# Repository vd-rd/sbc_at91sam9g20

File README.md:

View this project on [CADLAB.io](https://cadlab.io/project/30536). 

# Microchip AT91SAM9G20

## Description
 The follow-up to my previous [SBC based on AT91SAM9260](https://github.com/vd-rd/sbc_at91sam9260), enhancing the board specs in computing power and flexibility. The board is smaller 60x40mm now (SAM9260 was 80x40mm) while keeping the same amount of supported RAM and interfaces. AT91SAM9G20 boosts core speed to 400MHz and bus speed to 133MHz.
 
Board overview (draft):
[TBD]

### Features

| Characteristic | Description |
| --- | --- |
| Dimensions | 60mm x 40mm |
| Processor | AT91SAM9G20 - ARM926EJ @ 400MHz |
| Oscillators |  18.432MHz main clock, 32.768kHz RTC |
| RAM | SDRAM 128MB max (2x512Mbit modules) |
| Storage | microSD |
| USB | 1 microUSB client, 2 USB Host|
| Ethernet | RMII header |
| WiFi/BT | N/A |
| Supply | USB 5V, ACIN 5V |

Common interfaces such as I2C, SPI, UART and GPIO are exposed on the header.

### Building and flashing

Build U-Boot and Linux kernel + rootFS - TBD

Flash to SDCard - TBD

### Resources

You can find all necesary information to build or evaluate the module here:
   - [Fabrication files](https://github.com/vd-rd/sbc_alw_a13/releases)

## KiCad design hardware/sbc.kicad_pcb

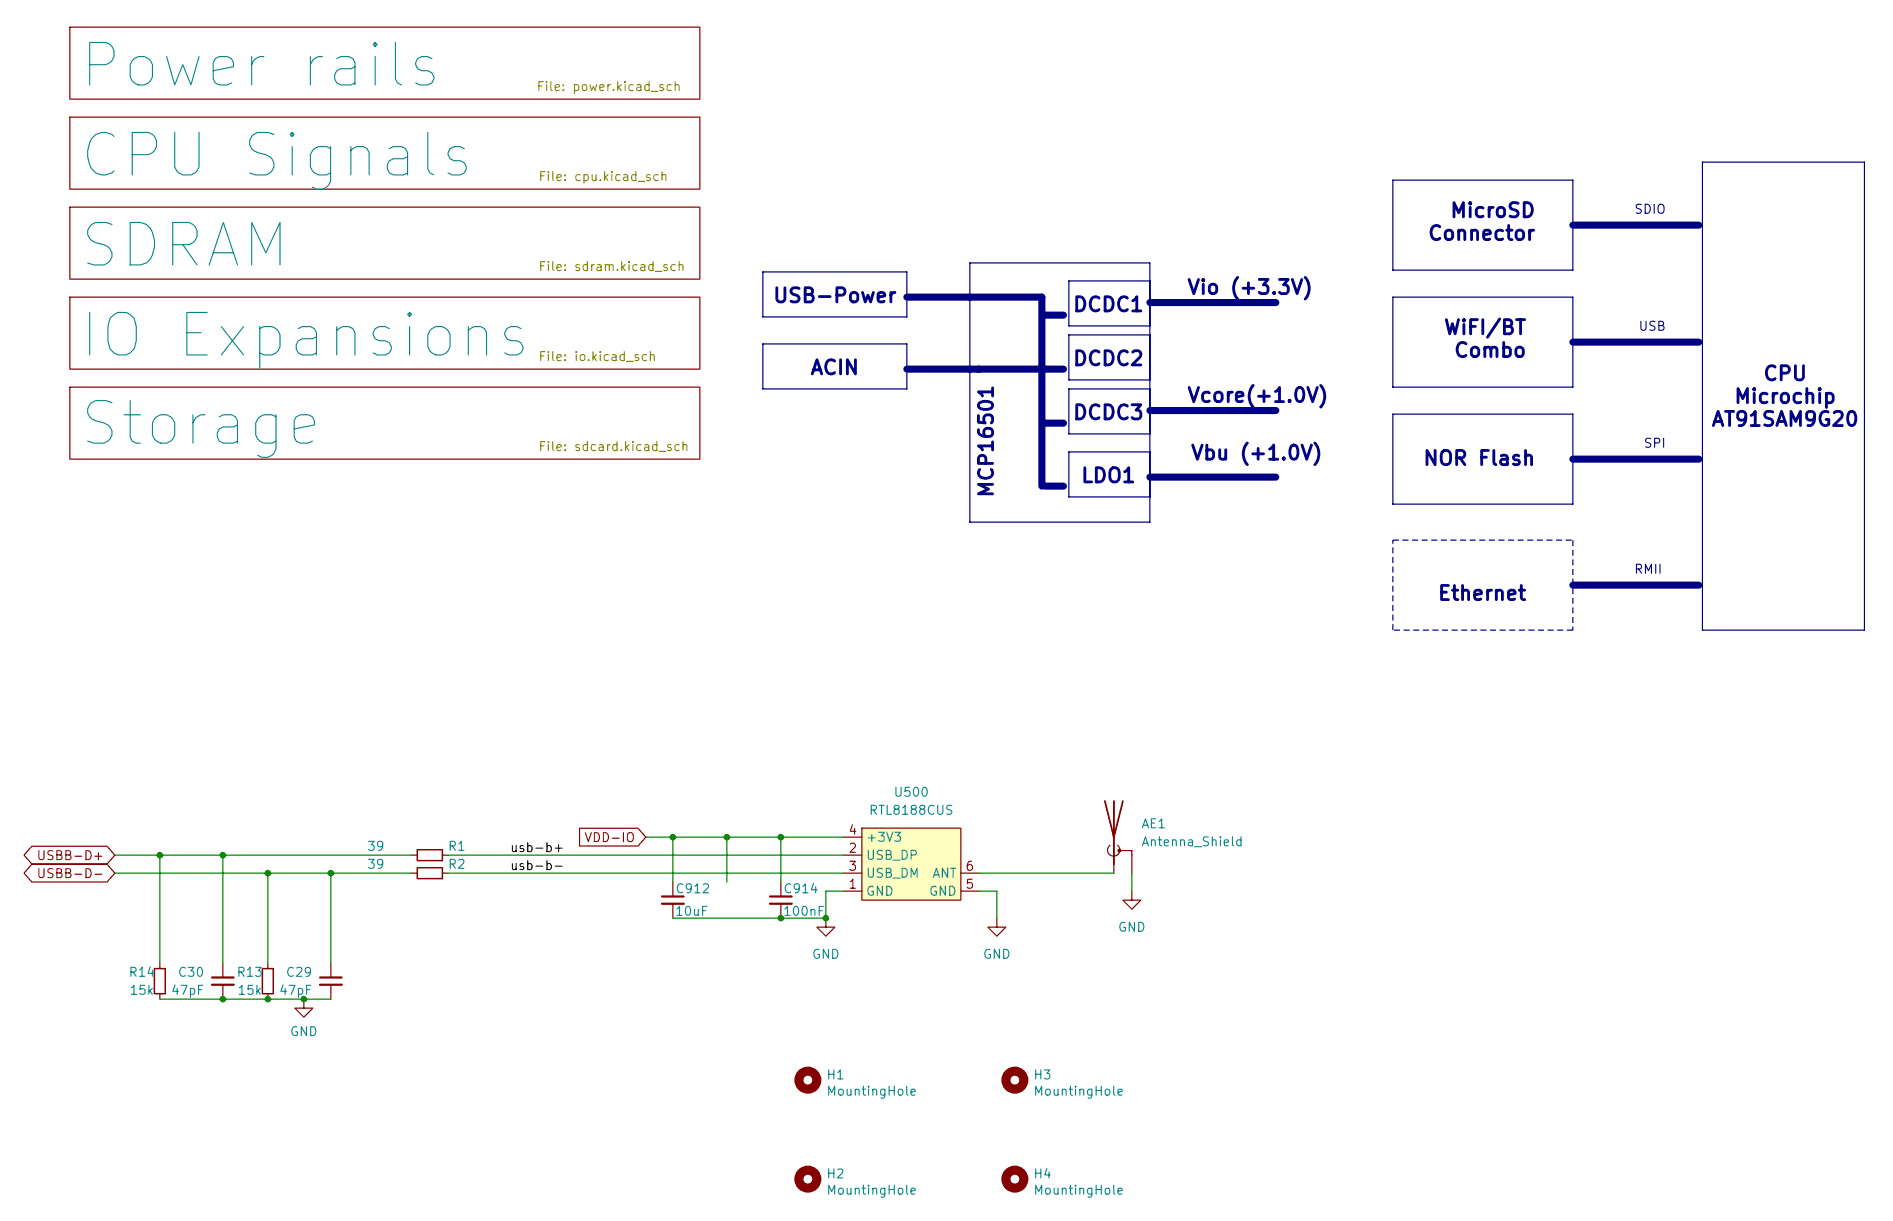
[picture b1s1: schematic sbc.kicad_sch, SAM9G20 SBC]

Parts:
AE1: Antenna_Shield; U.FL_Hirose_U.FL-R-SMT-1_Vertical
C29, C30: 47pF; C_0402_1005Metric
C912: 10uF; C_0603_1608Metric
C914: 100nF; C_0402_1005Metric
H1, H2, H3, H4: MountingHole; MountingHole_2.7mm_M2.5_DIN965
R1, R2: 39; R_0402_1005Metric
R13, R14: 15k; R_0402_1005Metric
U500: RTL8188CUS

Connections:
/usb-b+: R1.1, U500.2 (USB_DP)
/usb-b-: R2.1, U500.3 (USB_DM)
GND: AE1.2 (Shield), C29.2, C30.2, C912.2, C914.2, R13.2, R14.2, U500.1 (GND), U500.5 (GND); also elsewhere on the board
unnamed: AE1.1 (A), U500.6 (ANT)
USBB-D+: C30.1, R1.2, R14.1; also elsewhere on the board
USBB-D-: C29.1, R2.2, R13.1; also elsewhere on the board
VDD-IO: C912.1, C914.1, U500.4 (+3V3); also elsewhere on the board

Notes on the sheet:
Vbu (+1.0V)
DCDC3
USB-Power
NOR Flash
MCP16501
CPU Microchip AT91SAM9G20
Ethernet
ACIN
USB
WiFI/BT Combo
DCDC2
Vcore(+1.0V)
LDO1
DCDC1
MicroSD Connector
SPI
RMII
Vio (+3.3V)
SDIO

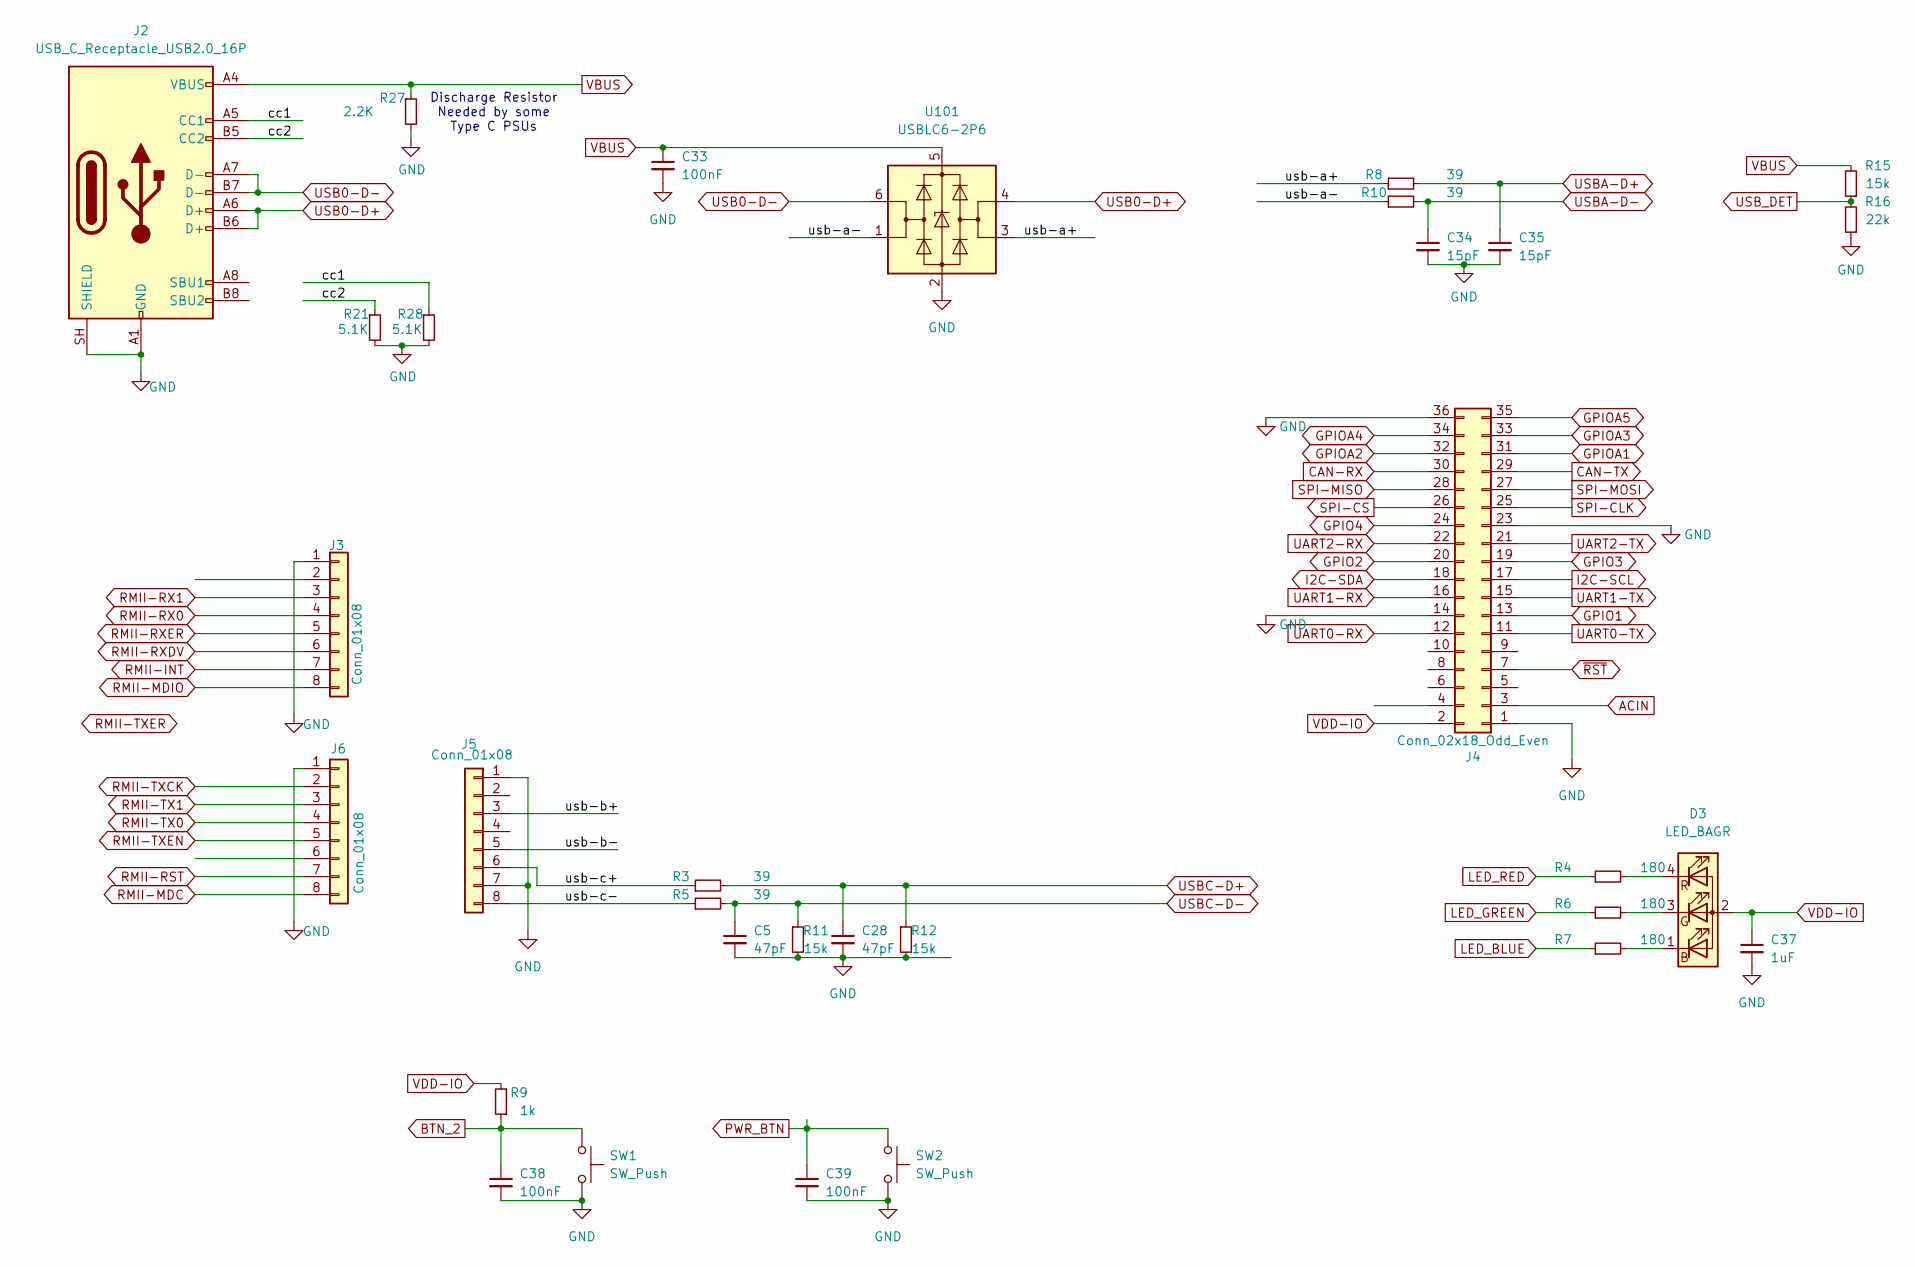
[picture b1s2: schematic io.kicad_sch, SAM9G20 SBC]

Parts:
C5, C28: 47pF; C_0402_1005Metric
C33, C38, C39: 100nF; C_0402_1005Metric
C34, C35: 15pF; C_0402_1005Metric
C37: 1uF; C_0402_1005Metric
D3: LED_BAGR; LED_RGB_Optosupply_OSTB0805C1E-A-0.8T
J2: USB_C_Receptacle_USB2.0_16P; USB_C_Receptacle_GCT_USB4105-xx-A_16P_TopMnt_Horizontal
J3, J5, J6: Conn_01x08; PinHeader_2x04_P1.27mm_Vertical
J4: Conn_02x18_Odd_Even; PinHeader_2x18_P2.54mm_Vertical
R3, R5, R8, R10: 39; R_0402_1005Metric
R4, R6, R7: 180; R_0402_1005Metric
R9: 1k; R_0402_1005Metric
R11, R12, R15: 15k; R_0402_1005Metric
R16: 22k; R_0402_1005Metric
R21, R28: 5.1K; R_0402_1005Metric; Part Description Resistor 2.2K M1005 1% 63mW
R27: 2.2K; R_0402_1005Metric; Part Description Resistor 2.2K M1005 1% 63mW
SW1, SW2: SW_Push; SW_SPST_EVQP7C
U101: USBLC6-2P6; SOT-23-6

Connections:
/IO Expansions/cc1: J2.A5 (CC1), R28.1
/IO Expansions/cc2: J2.B5 (CC2), R21.1
/IO Expansions/usb-a+: R8.1, U101.3 (I/O2)
/IO Expansions/usb-a-: R10.1, U101.1 (I/O1)
/IO Expansions/usb-b+: J5.3
/IO Expansions/usb-b-: J5.5
/IO Expansions/usb-c+: J5.6, R3.1
/IO Expansions/usb-c-: J5.8, R5.1
ACIN: J4.3; also elsewhere on the board
BTN_2: C38.1, R9.1, SW1.1; also elsewhere on the board
CAN-RX: J4.30
CAN-TX: J4.29
GND: C5.2, C28.2, C33.2, C34.2, C35.2, C37.2, C38.2, C39.2, J2.A1 (GND), J2.A12 (GND), J2.B1 (GND), J2.B12 (GND), J2.SH (SHIELD), J3.1, J4.1, J4.14, J4.23, J4.36, J5.1, J5.7, J6.1, R11.2, R12.2, R16.1, R21.2, R27.2, R28.2, SW1.2, SW2.2, U101.2 (GND); also elsewhere on the board
GPIO1: J4.13; also elsewhere on the board
GPIO2: J4.20; also elsewhere on the board
GPIO3: J4.19; also elsewhere on the board
GPIO4: J4.24; also elsewhere on the board
GPIOA1: J4.31; also elsewhere on the board
GPIOA2: J4.32; also elsewhere on the board
GPIOA3: J4.33; also elsewhere on the board
GPIOA4: J4.34; also elsewhere on the board
GPIOA5: J4.35
I2C-SCL: J4.17; also elsewhere on the board
I2C-SDA: J4.18; also elsewhere on the board
LED_BLUE: R7.1; also elsewhere on the board
LED_GREEN: R6.1; also elsewhere on the board
LED_RED: R4.1; also elsewhere on the board
unnamed: D3.1 (BK), R7.2
unnamed: D3.3 (GK), R6.2
unnamed: D3.4 (RK), R4.2
PWR_BTN: C39.1, SW2.1; also elsewhere on the board
RMII-INT: J3.7
RMII-MDC: J6.8; also elsewhere on the board
RMII-MDIO: J3.8; also elsewhere on the board
RMII-RST: J6.7
RMII-RX0: J3.4; also elsewhere on the board
RMII-RX1: J3.3; also elsewhere on the board
RMII-RXDV: J3.6; also elsewhere on the board
RMII-RXER: J3.5; also elsewhere on the board
RMII-TX0: J6.4; also elsewhere on the board
RMII-TX1: J6.3; also elsewhere on the board
RMII-TXCK: J6.2; also elsewhere on the board
RMII-TXEN: J6.5; also elsewhere on the board
SPI-CLK: J4.25; also elsewhere on the board
SPI-CS: J4.26; also elsewhere on the board
SPI-MISO: J4.28; also elsewhere on the board
SPI-MOSI: J4.27; also elsewhere on the board
UART0-RX: J4.12; also elsewhere on the board
UART0-TX: J4.11; also elsewhere on the board
UART1-RX: J4.16; also elsewhere on the board
UART1-TX: J4.15; also elsewhere on the board
UART2-RX: J4.22; also elsewhere on the board
UART2-TX: J4.21; also elsewhere on the board
USB0-D+: J2.A6 (D+), J2.B6 (D+), U101.4 (I/O2)
USB0-D-: J2.A7 (D-), J2.B7 (D-), U101.6 (I/O1)
USBA-D+: C35.1, R8.2; also elsewhere on the board
USBA-D-: C34.1, R10.2; also elsewhere on the board
USBC-D+: C28.1, R3.2, R12.1; also elsewhere on the board
USBC-D-: C5.1, R5.2, R11.1; also elsewhere on the board
USB_DET: R15.1, R16.2; also elsewhere on the board
VBUS: C33.1, J2.A4 (VBUS), J2.A9 (VBUS), J2.B4 (VBUS), J2.B9 (VBUS), R15.2, R27.1, U101.5 (VBUS); also elsewhere on the board
VDD-IO: C37.1, D3.2 (A), J4.2, R9.2; also elsewhere on the board
~RST: J4.7; also elsewhere on the board

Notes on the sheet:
Discharge Resistor Needed by some Type C PSUs

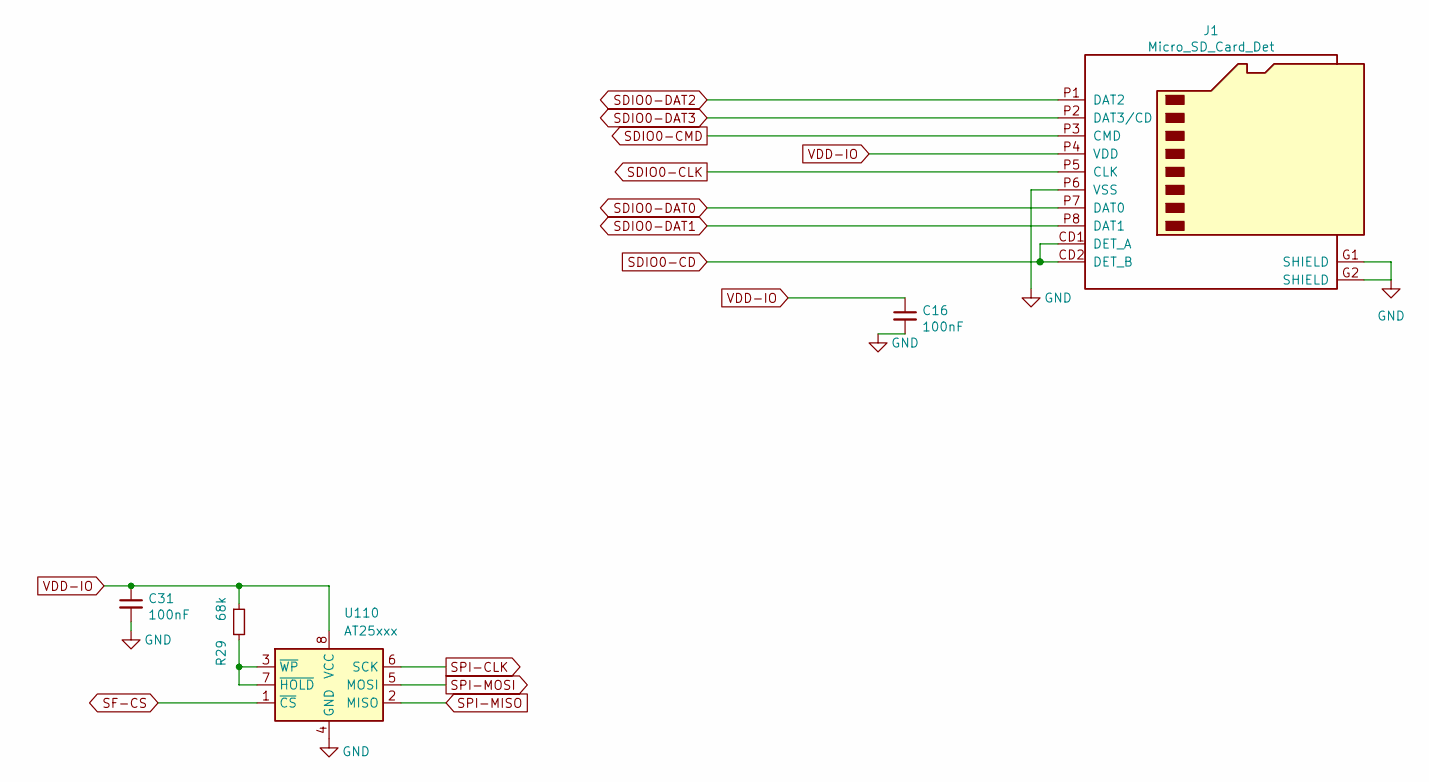
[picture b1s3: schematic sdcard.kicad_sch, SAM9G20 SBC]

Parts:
C16, C31: 100nF; C_0402_1005Metric
J1: Micro_SD_Card_Det; MEM20610118800A
R29: 68k; R_0402_1005Metric
U110: AT25xxx; SOIC-8_5.23x5.23mm_P1.27mm

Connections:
GND: C16.2, C31.2, J1.G1 (SHIELD), J1.G2 (SHIELD), J1.P6 (VSS), U110.4 (GND); also elsewhere on the board
unnamed: R29.2, U110.3 (~WP), U110.7 (~HOLD)
SDIO0-CD: J1.CD1 (DET_A), J1.CD2 (DET_B); also elsewhere on the board
SDIO0-CLK: J1.P5 (CLK); also elsewhere on the board
SDIO0-CMD: J1.P3 (CMD); also elsewhere on the board
SDIO0-DAT0: J1.P7 (DAT0); also elsewhere on the board
SDIO0-DAT1: J1.P8 (DAT1); also elsewhere on the board
SDIO0-DAT2: J1.P1 (DAT2); also elsewhere on the board
SDIO0-DAT3: J1.P2 (DAT3/CD); also elsewhere on the board
SF-CS: U110.1 (~CS); also elsewhere on the board
SPI-CLK: U110.6 (SCK); also elsewhere on the board
SPI-MISO: U110.2 (MISO); also elsewhere on the board
SPI-MOSI: U110.5 (MOSI); also elsewhere on the board
VDD-IO: C16.1, C31.1, J1.P4 (VDD), R29.1, U110.8 (VCC); also elsewhere on the board

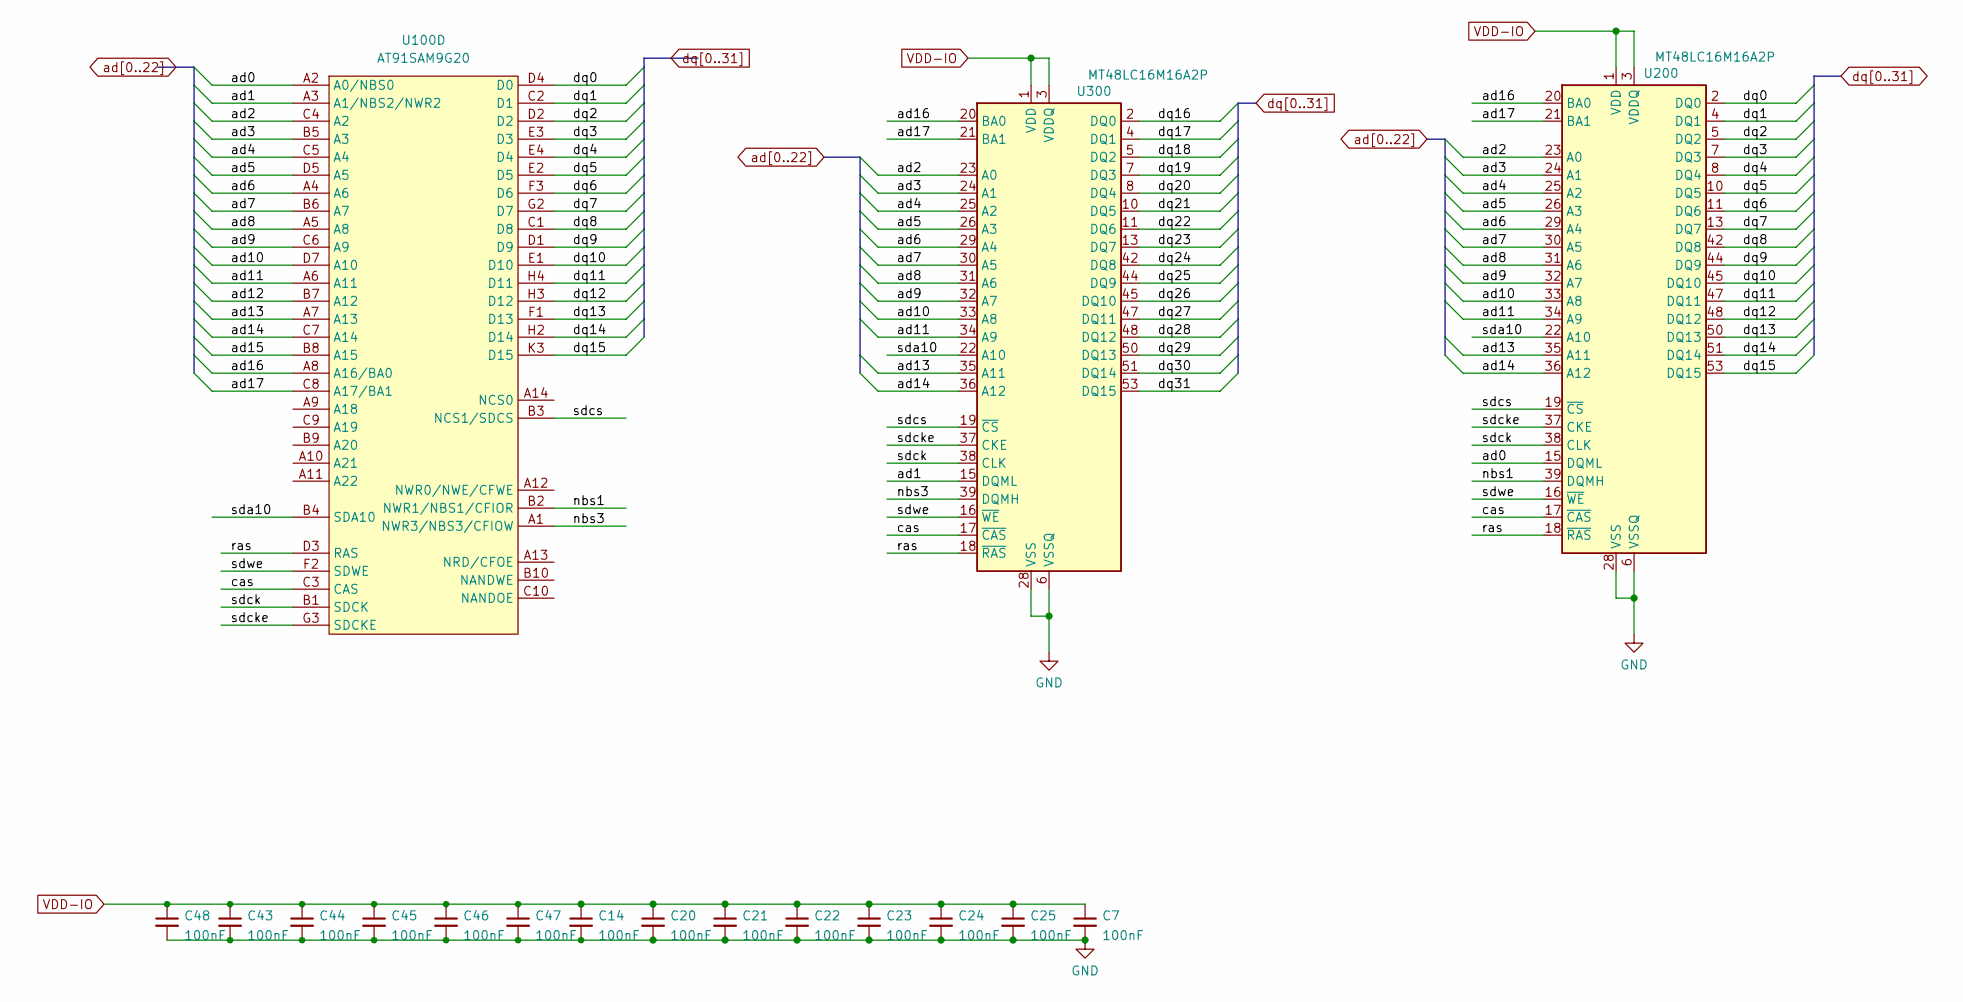
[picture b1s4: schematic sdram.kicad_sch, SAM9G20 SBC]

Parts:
C7, C14, C20, C21, C22, C23, C24, C25, C43, C44, C45, C46, C47, C48: 100nF; C_0402_1005Metric
U100: AT91SAM9G20; AT91SAM9G10
U200, U300: MT48LC16M16A2P; TSOP-II-54_22.2x10.16mm_P0.8mm

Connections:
/SDRAM/cas: U100.C3 (CAS), U200.17 (~CAS), U300.17 (~CAS)
/SDRAM/nbs1: U100.B2 (NWR1/NBS1/CFIOR), U200.39 (DQMH)
/SDRAM/nbs3: U100.A1 (NWR3/NBS3/CFIOW), U300.39 (DQMH)
/SDRAM/ras: U100.D3 (RAS), U200.18 (~RAS), U300.18 (~RAS)
/SDRAM/sda10: U100.B4 (SDA10), U200.22 (A10), U300.22 (A10)
/SDRAM/sdck: U100.B1 (SDCK), U200.38 (CLK), U300.38 (CLK)
/SDRAM/sdcke: U100.G3 (SDCKE), U200.37 (CKE), U300.37 (CKE)
/SDRAM/sdcs: U100.B3 (NCS1/SDCS), U200.19 (~CS), U300.19 (~CS)
/SDRAM/sdwe: U100.F2 (SDWE), U200.16 (~WE), U300.16 (~WE)
GND: C7.2, C14.2, C20.2, C21.2, C22.2, C23.2, C24.2, C25.2, C43.2, C44.2, C45.2, C46.2, C47.2, C48.2, U200.6 (VSSQ), U200.12 (VSSQ), U200.28 (VSS), U200.41 (VSS), U200.46 (VSSQ), U200.52 (VSSQ), U200.54 (VSS), U300.6 (VSSQ), U300.12 (VSSQ), U300.28 (VSS), U300.41 (VSS), U300.46 (VSSQ), U300.52 (VSSQ), U300.54 (VSS); also elsewhere on the board
VDD-IO: C7.1, C14.1, C20.1, C21.1, C22.1, C23.1, C24.1, C25.1, C43.1, C44.1, C45.1, C46.1, C47.1, C48.1, U200.1 (VDD), U200.3 (VDDQ), U200.9 (VDDQ), U200.14 (VDD), U200.27 (VDD), U200.43 (VDDQ), U200.49 (VDDQ), U300.1 (VDD), U300.3 (VDDQ), U300.9 (VDDQ), U300.14 (VDD), U300.27 (VDD), U300.43 (VDDQ), U300.49 (VDDQ); also elsewhere on the board
ad0: U100.A2 (A0/NBS0), U200.15 (DQML)
ad1: U100.A3 (A1/NBS2/NWR2), U300.15 (DQML)
ad2: U100.C4 (A2), U200.23 (A0), U300.23 (A0)
ad3: U100.B5 (A3), U200.24 (A1), U300.24 (A1)
ad4: U100.C5 (A4), U200.25 (A2), U300.25 (A2)
ad5: U100.D5 (A5), U200.26 (A3), U300.26 (A3)
ad6: U100.A4 (A6), U200.29 (A4), U300.29 (A4)
ad7: U100.B6 (A7), U200.30 (A5), U300.30 (A5)
ad8: U100.A5 (A8), U200.31 (A6), U300.31 (A6)
ad9: U100.C6 (A9), U200.32 (A7), U300.32 (A7)
ad10: U100.D7 (A10), U200.33 (A8), U300.33 (A8)
ad11: U100.A6 (A11), U200.34 (A9), U300.34 (A9)
ad12: U100.B7 (A12)
ad13: U100.A7 (A13), U200.35 (A11), U300.35 (A11)
ad14: U100.C7 (A14), U200.36 (A12), U300.36 (A12)
ad15: U100.B8 (A15)
ad16: U100.A8 (A16/BA0), U200.20 (BA0), U300.20 (BA0)
ad17: U100.C8 (A17/BA1), U200.21 (BA1), U300.21 (BA1)
dq0: U100.D4 (D0), U200.2 (DQ0)
dq1: U100.C2 (D1), U200.4 (DQ1)
dq2: U100.D2, U200.5 (DQ2)
dq3: U100.E3 (D3), U200.7 (DQ3)
dq4: U100.E4 (D4), U200.8 (DQ4)
dq5: U100.E2 (D5), U200.10 (DQ5)
dq6: U100.F3 (D6), U200.11 (DQ6)
dq7: U100.G2 (D7), U200.13 (DQ7)
dq8: U100.C1 (D8), U200.42 (DQ8)
dq9: U100.D1 (D9), U200.44 (DQ9)
dq10: U100.E1 (D10), U200.45 (DQ10)
dq11: U100.H4 (D11), U200.47 (DQ11)
dq12: U100.H3 (D12), U200.48 (DQ12)
dq13: U100.F1 (D13), U200.50 (DQ13)
dq14: U100.H2 (D14), U200.51 (DQ14)
dq15: U100.K3 (D15), U200.53 (DQ15)
dq16: U300.2 (DQ0); also elsewhere on the board
dq17: U300.4 (DQ1); also elsewhere on the board
dq18: U300.5 (DQ2); also elsewhere on the board
dq19: U300.7 (DQ3); also elsewhere on the board
dq20: U300.8 (DQ4); also elsewhere on the board
dq21: U300.10 (DQ5); also elsewhere on the board
dq22: U300.11 (DQ6); also elsewhere on the board
dq23: U300.13 (DQ7); also elsewhere on the board
dq24: U300.42 (DQ8); also elsewhere on the board
dq25: U300.44 (DQ9); also elsewhere on the board
dq26: U300.45 (DQ10); also elsewhere on the board
dq27: U300.47 (DQ11); also elsewhere on the board
dq28: U300.48 (DQ12); also elsewhere on the board
dq29: U300.50 (DQ13); also elsewhere on the board
dq30: U300.51 (DQ14); also elsewhere on the board
dq31: U300.53 (DQ15); also elsewhere on the board

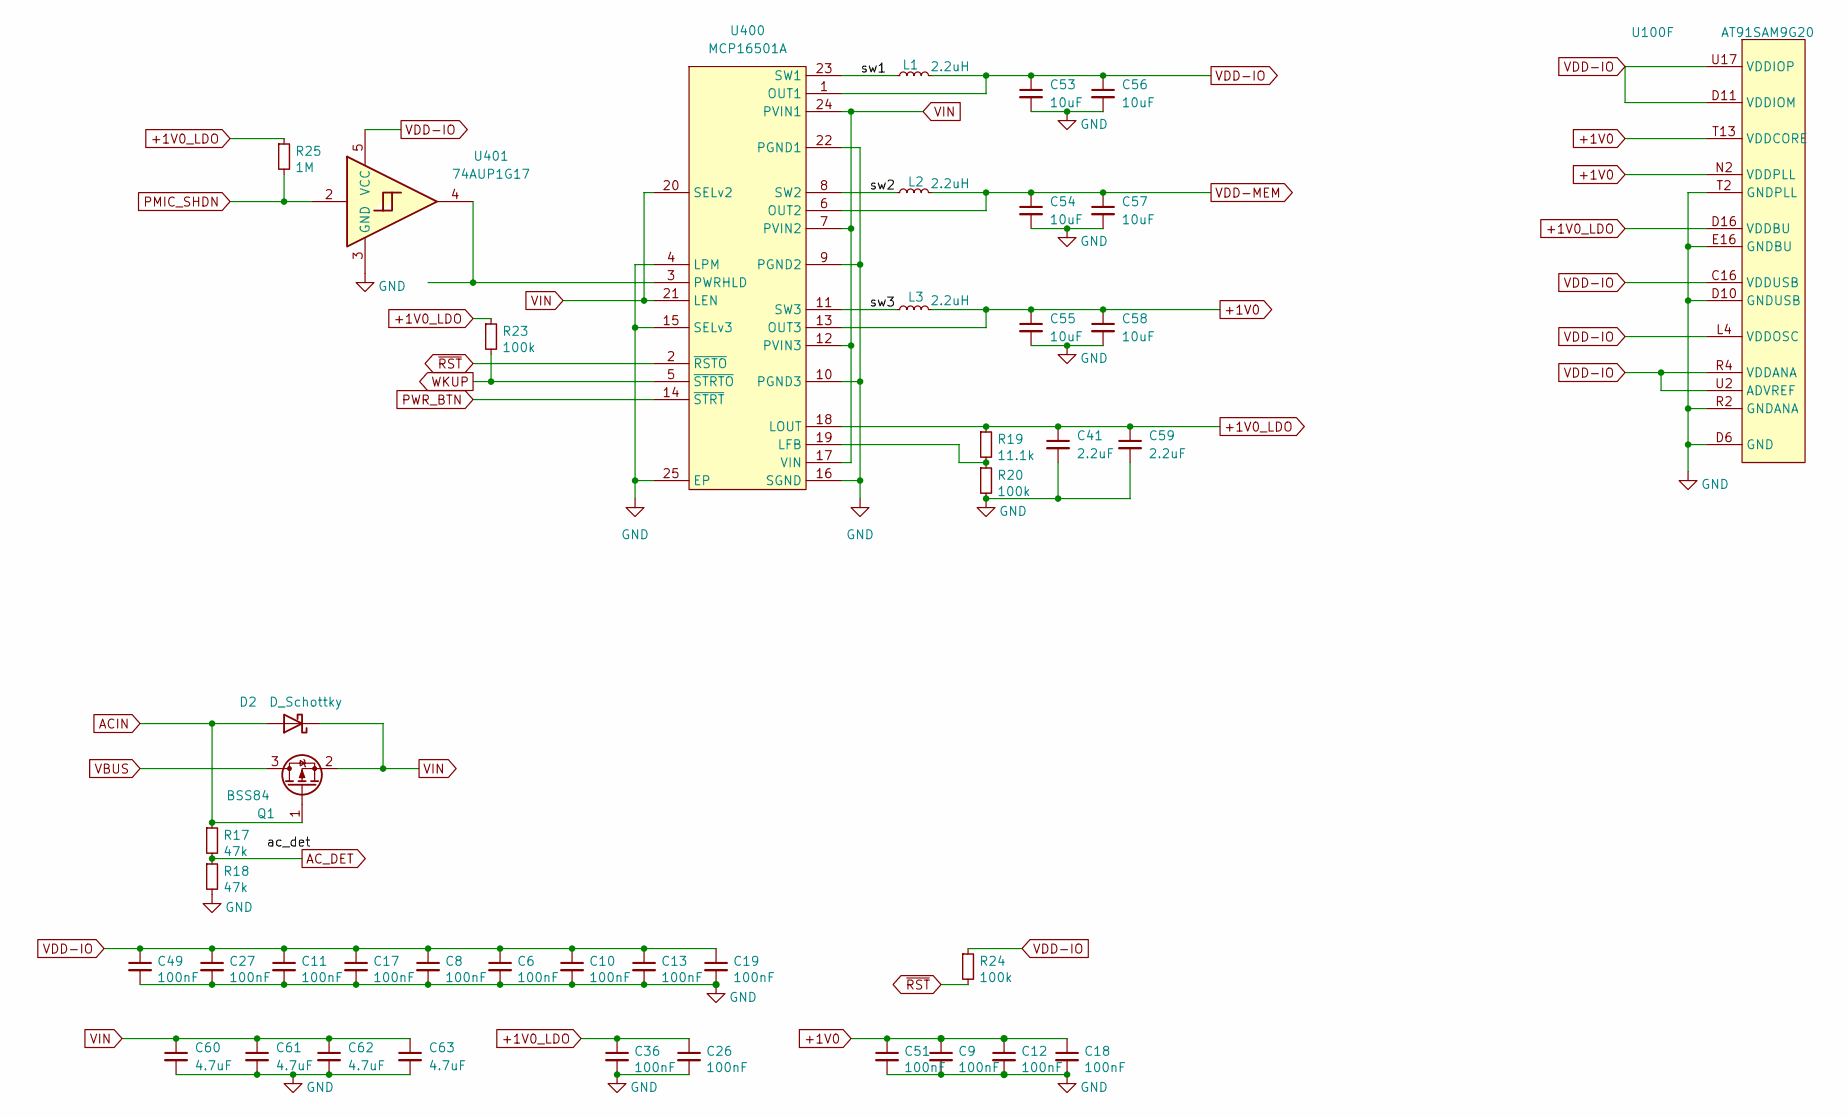
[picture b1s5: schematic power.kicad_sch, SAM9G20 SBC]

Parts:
C6, C8, C9, C10, C11, C12, C13, C17, C18, C19, C26, C27, C36, C49, C51: 100nF; C_0402_1005Metric
C41, C59: 2.2uF; C_0402_1005Metric
C53, C54, C55, C56, C57, C58: 10uF; C_0603_1608Metric
C60, C61, C62, C63: 4.7uF; C_0603_1608Metric
D2: D_Schottky; D_SOD-323
L1, L2, L3: 2.2uH; L_Wuerth_MAPI-2512
Q1: BSS84; SOT-323_SC-70
R17, R18: 47k; R_0402_1005Metric
R19: 11.1k; R_0402_1005Metric
R20, R23, R24: 100k; R_0402_1005Metric
R25: 1M; R_0402_1005Metric
U100: AT91SAM9G20; AT91SAM9G10
U400: MCP16501A; QFN-24-1EP_4x4mm_P0.5mm_EP2.7x2.7mm_ThermalVias
U401: 74AUP1G17; Texas_R-PDSO-N5_DRL-5

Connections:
+1V0: C9.1, C12.1, C18.1, C51.1, C55.1, C58.1, L3.2, U100.D9 (VDDCORE), U100.H14 (VDDCORE), U100.M1 (VDDCORE), U100.N2 (VDDPLL), U100.P2 (VDDPLL), U100.T13 (VDDCORE), U400.13 (OUT3)
+1V0_LDO: C26.1, C36.1, C41.1, C59.1, R19.1, R23.1, R25.1, U100.D16 (VDDBU), U400.18 (LOUT); also elsewhere on the board
/Power rails/sw1: L1.1, U400.23 (SW1)
/Power rails/sw2: L2.1, U400.8 (SW2)
/Power rails/sw3: L3.1, U400.11 (SW3)
ACIN: D2.2 (A), Q1.1 (G), R17.1; also elsewhere on the board
AC_DET: R17.2, R18.1; also elsewhere on the board
GND: C6.2, C8.2, C9.2, C10.2, C11.2, C12.2, C13.2, C17.2, C18.2, C19.2, C26.2, C27.2, C36.2, C41.2, C49.2, C51.2, C53.2, C54.2, C55.2, C56.2, C57.2, C58.2, C59.2, C60.2, C61.2, C62.2, C63.2, R18.2, R20.2, U100.D6 (GND), U100.D8 (GND), U100.D10 (GNDUSB), U100.D12 (GNDUSB), U100.E16 (GNDBU), U100.F4 (GND), U100.G14 (GND), U100.H8 (GND), U100.H9 (GND), U100.H10 (GND), U100.J8 (GND), U100.J9 (GND), U100.J10 (GND), U100.K8 (GND), U100.K9 (GND), U100.K10 (GND), U100.K16 (GND), U100.L1 (GND), U100.M3 (GND), U100.R2 (GNDANA), U100.R7 (GND), U100.T2 (GNDPLL), U100.T7 (GND), U100.T15 (GND), U100.U1 (GNDPLL), U400.4 (LPM), U400.9 (PGND2), U400.10 (PGND3), U400.15 (SELv3), U400.16 (SGND), U400.22 (PGND1), U400.25 (EP), U401.3 (GND); also elsewhere on the board
unnamed: R19.2, R20.1, U400.19 (LFB)
unnamed: U400.3 (PWRHLD), U401.4
PMIC_SHDN: R25.2, U401.2; also elsewhere on the board
PWR_BTN: U400.14 (~STRT); also elsewhere on the board
VBUS: Q1.3 (D); also elsewhere on the board
VDD-IO: C6.1, C8.1, C10.1, C11.1, C13.1, C17.1, C19.1, C27.1, C49.1, C53.1, C56.1, L1.2, R24.1, U100.C16 (VDDUSB), U100.D11 (VDDIOM), U100.G4 (VDDIOM), U100.J3 (VDDIOM), U100.L4 (VDDOSC), U100.P8 (VDDIOP), U100.R4 (VDDANA), U100.U2 (ADVREF), U100.U17 (VDDIOP), U400.1 (OUT1), U401.5 (VCC); also elsewhere on the board
VDD-MEM: C54.1, C57.1, L2.2, U400.6 (OUT2)
VIN: C60.1, C61.1, C62.1, C63.1, D2.1 (K), Q1.2 (S), U400.7 (PVIN2), U400.12 (PVIN3), U400.17 (VIN), U400.20 (SELv2), U400.21 (LEN), U400.24 (PVIN1)
WKUP: R23.2, U400.5 (~STRTO); also elsewhere on the board
~RST: R24.2, U400.2 (~RSTO); also elsewhere on the board

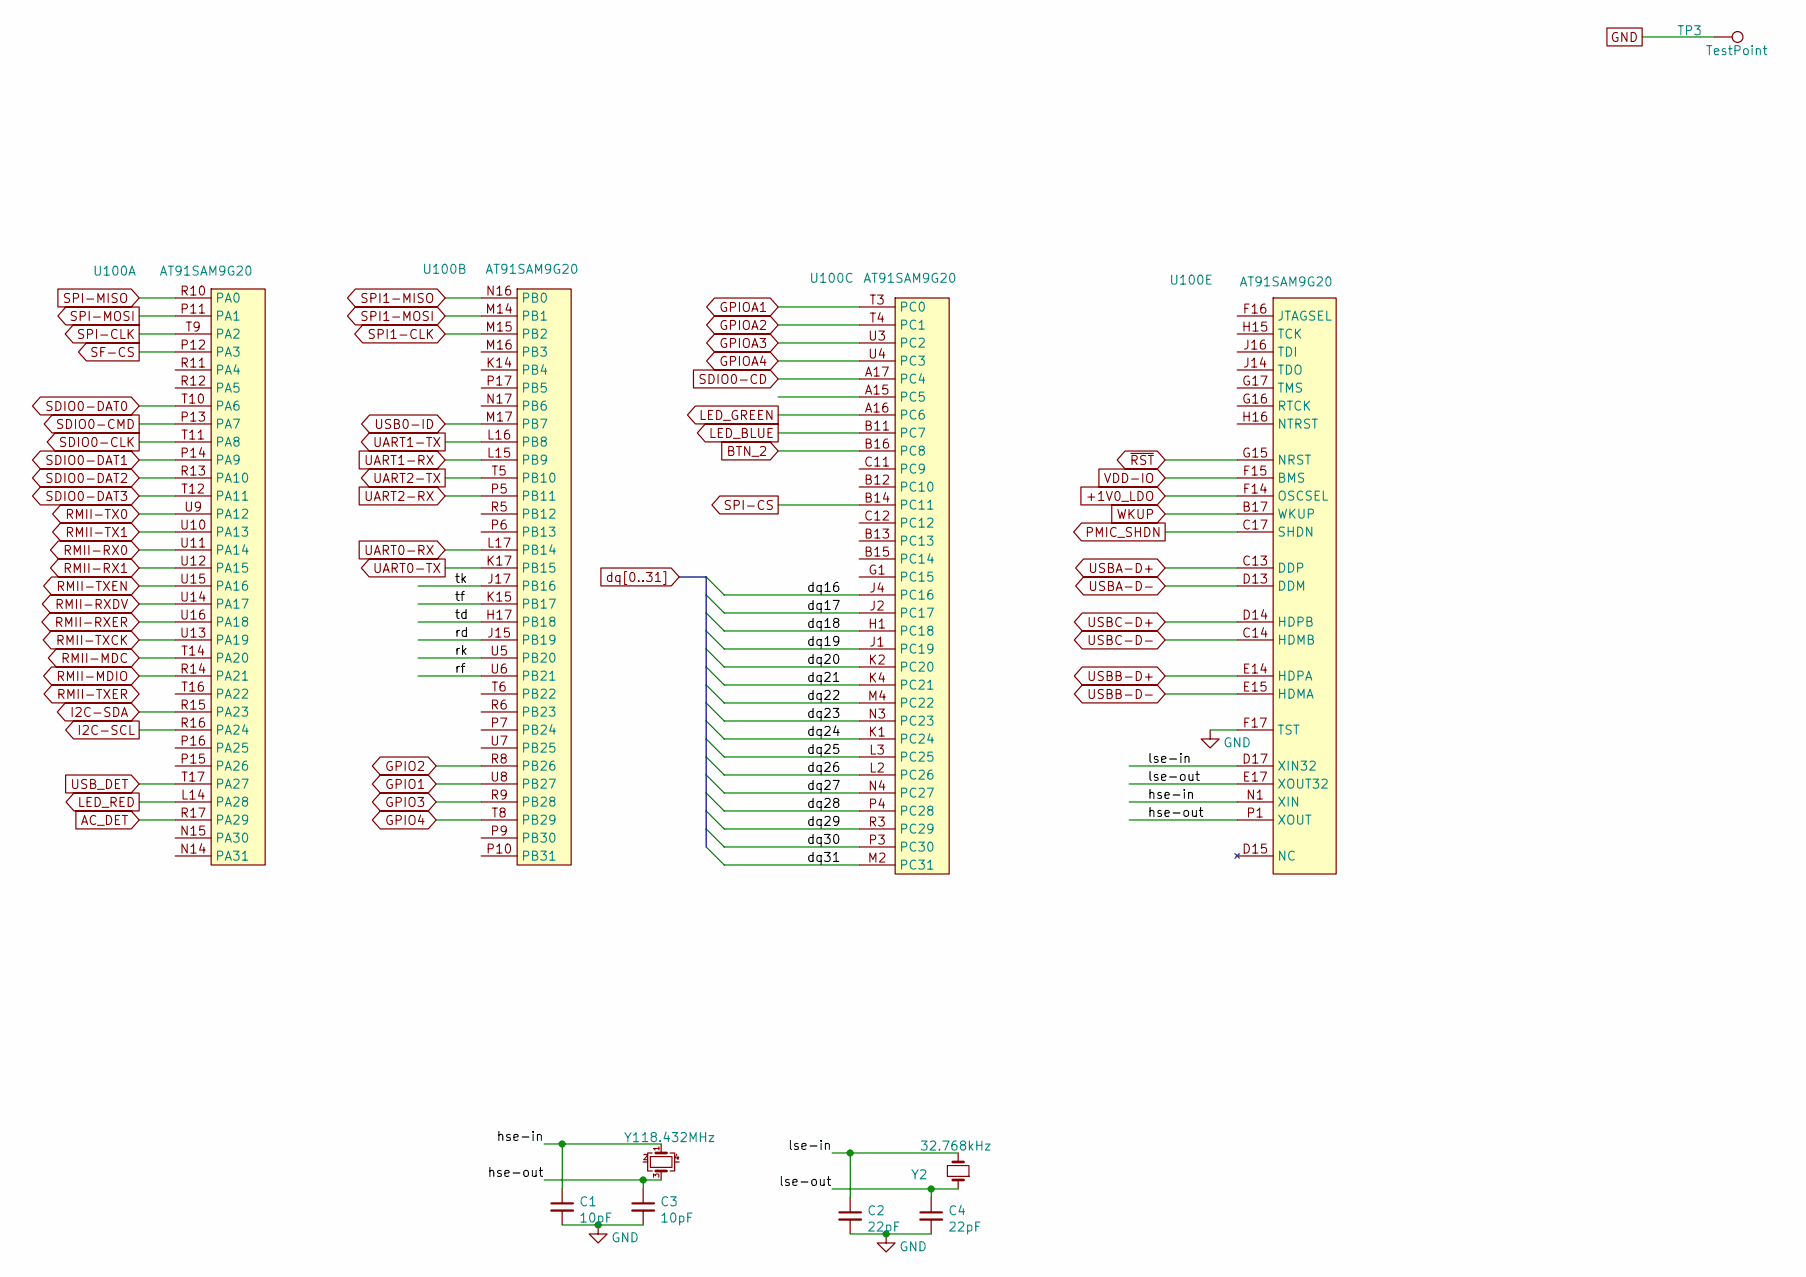
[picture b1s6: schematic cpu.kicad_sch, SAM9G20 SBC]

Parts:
C1, C3: 10pF; C_0402_1005Metric
C2, C4: 22pF; C_0402_1005Metric
TP3: TestPoint; TestPoint_Pad_D1.0mm
U100: AT91SAM9G20; AT91SAM9G10
Y1: 18.432MHz; Crystal_SMD_3225-4Pin_3.2x2.5mm
Y2: 32.768kHz; Crystal_SMD_3215-2Pin_3.2x1.5mm

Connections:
+1V0_LDO: U100.F14 (OSCSEL); also elsewhere on the board
/CPU Signals/hse-in: C1.1, U100.N1 (XIN), Y1.1
/CPU Signals/hse-out: C3.1, U100.P1 (XOUT), Y1.3
/CPU Signals/lse-in: C2.1, U100.D17 (XIN32), Y2.2
/CPU Signals/lse-out: C4.1, U100.E17 (XOUT32), Y2.1
/CPU Signals/rd: U100.J15 (PB19)
/CPU Signals/rf: U100.U6 (PB21)
/CPU Signals/rk: U100.U5 (PB20)
/CPU Signals/td: U100.H17 (PB18)
/CPU Signals/tf: U100.K15 (PB17)
/CPU Signals/tk: U100.J17 (PB16)
AC_DET: U100.R17 (PA29); also elsewhere on the board
BTN_2: U100.B16 (PC8); also elsewhere on the board
GND: C1.2, C2.2, C3.2, C4.2, TP3.1 (1_1), U100.F17 (TST); also elsewhere on the board
GPIO1: U100.U8 (PB27); also elsewhere on the board
GPIO2: U100.R8 (PB26); also elsewhere on the board
GPIO3: U100.R9 (PB28); also elsewhere on the board
GPIO4: U100.T8 (PB29); also elsewhere on the board
GPIOA1: U100.T3 (PC0); also elsewhere on the board
GPIOA2: U100.T4 (PC1); also elsewhere on the board
GPIOA3: U100.U3 (PC2); also elsewhere on the board
GPIOA4: U100.U4 (PC3); also elsewhere on the board
I2C-SCL: U100.R16 (PA24); also elsewhere on the board
I2C-SDA: U100.R15 (PA23); also elsewhere on the board
LED_BLUE: U100.B11 (PC7); also elsewhere on the board
LED_GREEN: U100.A16 (PC6); also elsewhere on the board
LED_RED: U100.L14 (PA28); also elsewhere on the board
PMIC_SHDN: U100.C17 (SHDN); also elsewhere on the board
RMII-MDC: U100.T14 (PA20); also elsewhere on the board
RMII-MDIO: U100.R14 (PA21); also elsewhere on the board
RMII-RX0: U100.U11 (PA14); also elsewhere on the board
RMII-RX1: U100.U12 (PA15); also elsewhere on the board
RMII-RXDV: U100.U14 (PA17); also elsewhere on the board
RMII-RXER: U100.U16 (PA18); also elsewhere on the board
RMII-TX0: U100.U9 (PA12); also elsewhere on the board
RMII-TX1: U100.U10 (PA13); also elsewhere on the board
RMII-TXCK: U100.U13 (PA19); also elsewhere on the board
RMII-TXEN: U100.U15 (PA16); also elsewhere on the board
SDIO0-CD: U100.A17 (PC4); also elsewhere on the board
SDIO0-CLK: U100.T11 (PA8); also elsewhere on the board
SDIO0-CMD: U100.P13 (PA7); also elsewhere on the board
SDIO0-DAT0: U100.T10 (PA6); also elsewhere on the board
SDIO0-DAT1: U100.P14 (PA9); also elsewhere on the board
SDIO0-DAT2: U100.R13 (PA10); also elsewhere on the board
SDIO0-DAT3: U100.T12 (PA11); also elsewhere on the board
SF-CS: U100.P12 (PA3); also elsewhere on the board
SPI1-CLK: U100.M15 (PB2)
SPI1-MISO: U100.N16 (PB0)
SPI1-MOSI: U100.M14 (PB1)
SPI-CLK: U100.T9 (PA2); also elsewhere on the board
SPI-CS: U100.B14 (PC11); also elsewhere on the board
SPI-MISO: U100.R10 (PA0); also elsewhere on the board
SPI-MOSI: U100.P11 (PA1); also elsewhere on the board
UART0-RX: U100.L17 (PB14); also elsewhere on the board
UART0-TX: U100.K17 (PB15); also elsewhere on the board
UART1-RX: U100.L15 (PB9); also elsewhere on the board
UART1-TX: U100.L16 (PB8); also elsewhere on the board
UART2-RX: U100.P5 (PB11); also elsewhere on the board
UART2-TX: U100.T5 (PB10); also elsewhere on the board
USB0-ID: U100.M17 (PB7)
USBA-D+: U100.C13 (DDP); also elsewhere on the board
USBA-D-: U100.D13 (DDM); also elsewhere on the board
USBB-D+: U100.E14 (HDPA); also elsewhere on the board
USBB-D-: U100.E15 (HDMA); also elsewhere on the board
USBC-D+: U100.D14 (HDPB); also elsewhere on the board
USBC-D-: U100.C14 (HDMB); also elsewhere on the board
USB_DET: U100.T17 (PA27); also elsewhere on the board
VDD-IO: U100.F15 (BMS); also elsewhere on the board
WKUP: U100.B17 (WKUP); also elsewhere on the board
dq16: U100.J4 (PC16); also elsewhere on the board
dq17: U100.J2 (PC17); also elsewhere on the board
dq18: U100.H1 (PC18); also elsewhere on the board
dq19: U100.J1 (PC19); also elsewhere on the board
dq20: U100.K2 (PC20); also elsewhere on the board
dq21: U100.K4 (PC21); also elsewhere on the board
dq22: U100.M4 (PC22); also elsewhere on the board
dq23: U100.N3 (PC23); also elsewhere on the board
dq24: U100.K1 (PC24); also elsewhere on the board
dq25: U100.L3 (PC25); also elsewhere on the board
dq26: U100.L2 (PC26); also elsewhere on the board
dq27: U100.N4 (PC27); also elsewhere on the board
dq28: U100.P4 (PC28); also elsewhere on the board
dq29: U100.R3 (PC29); also elsewhere on the board
dq30: U100.P3 (PC30); also elsewhere on the board
dq31: U100.M2 (PC31); also elsewhere on the board
~RST: U100.G15 (NRST); also elsewhere on the board

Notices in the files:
hardware/sbc.kicad_pcb:
© VDRD
